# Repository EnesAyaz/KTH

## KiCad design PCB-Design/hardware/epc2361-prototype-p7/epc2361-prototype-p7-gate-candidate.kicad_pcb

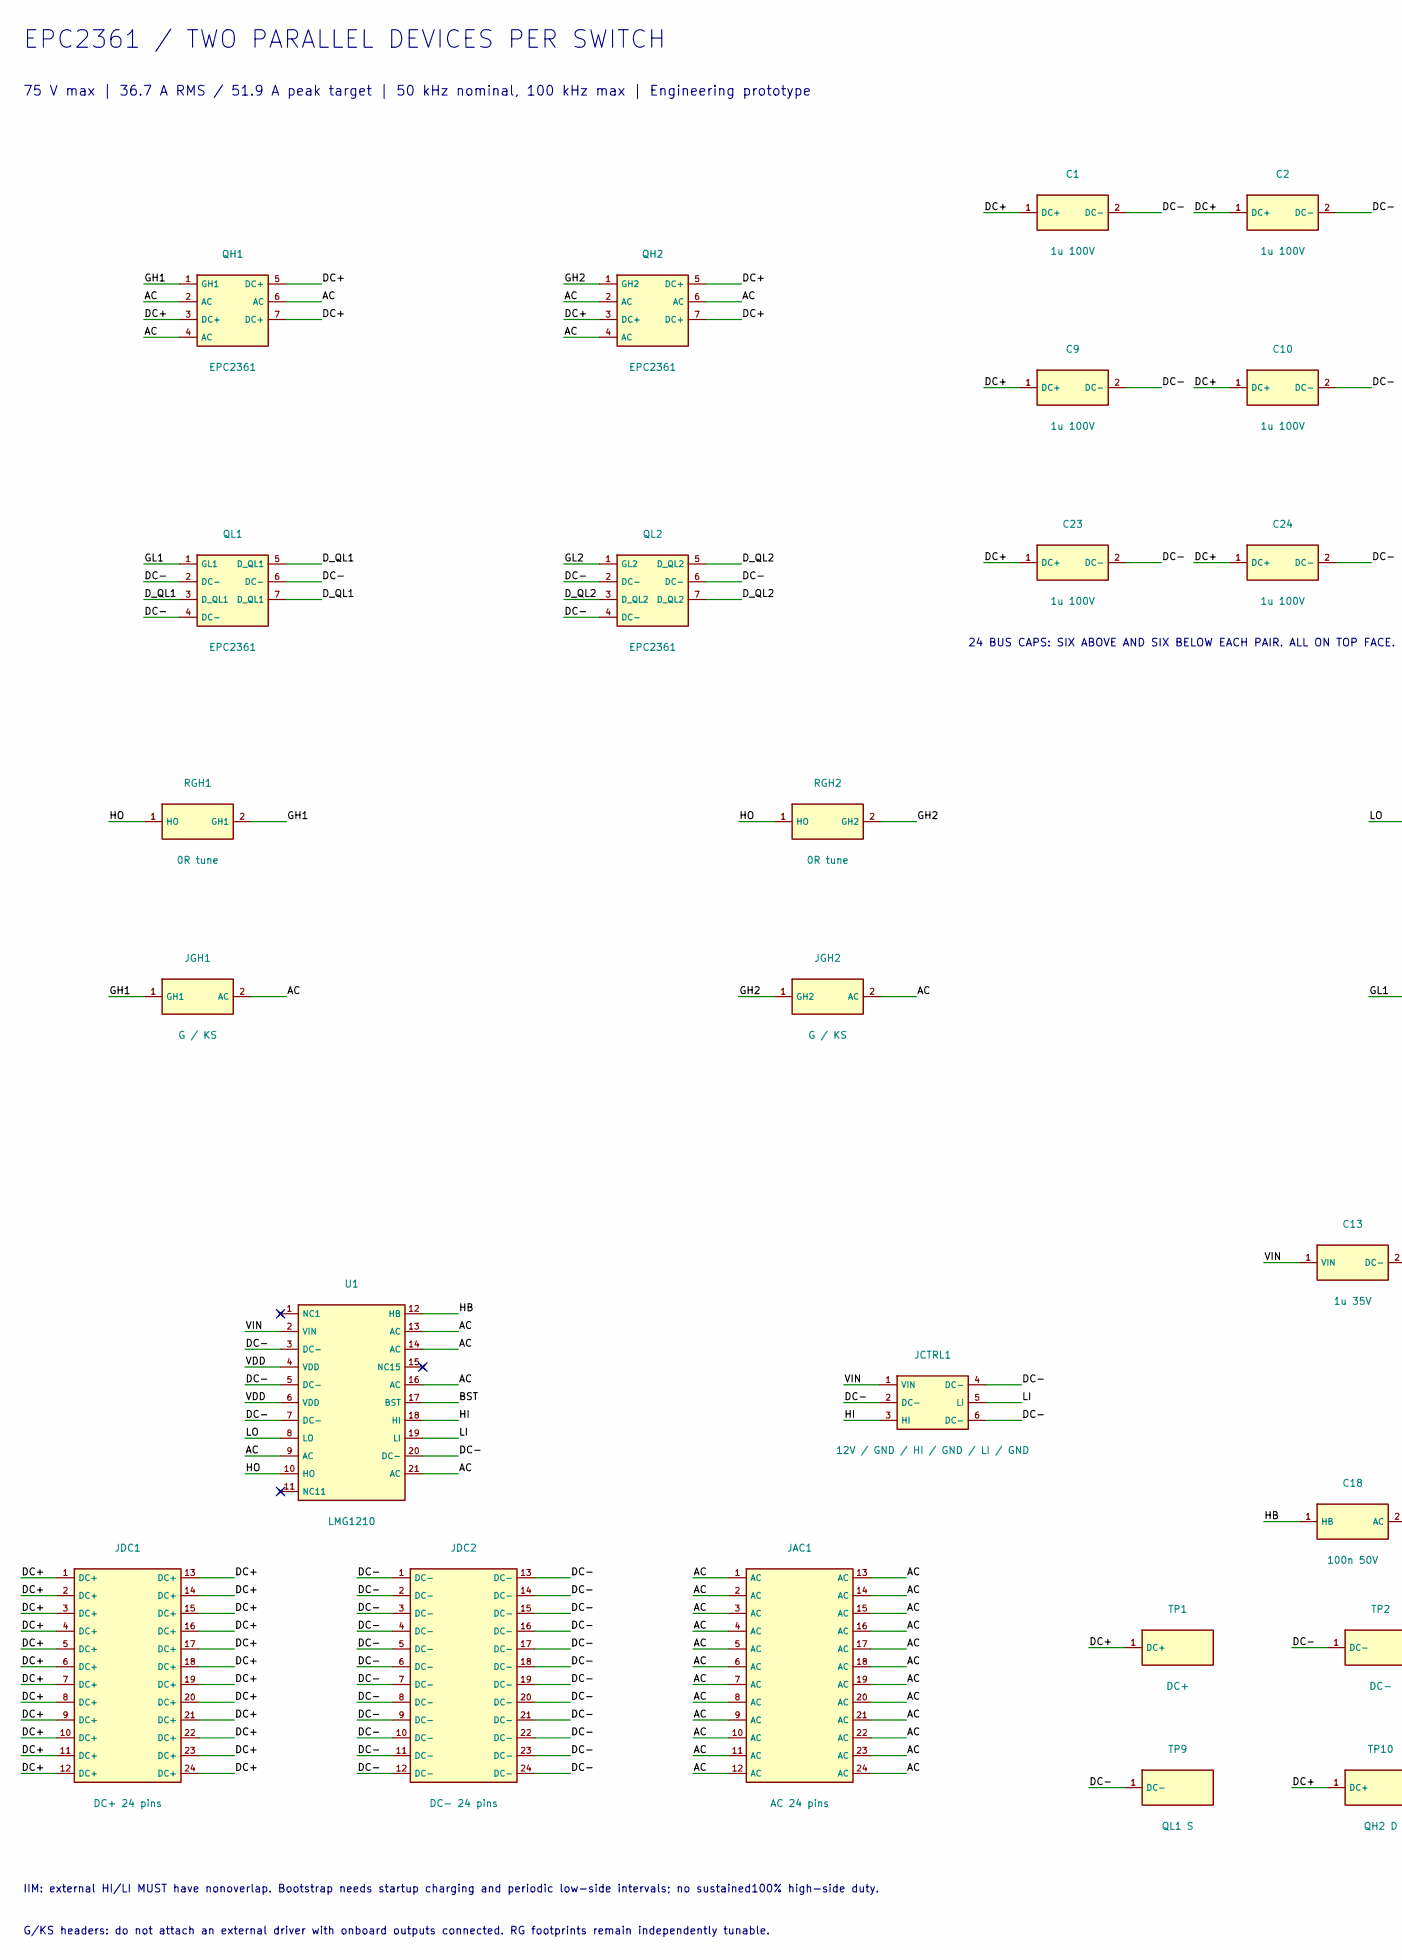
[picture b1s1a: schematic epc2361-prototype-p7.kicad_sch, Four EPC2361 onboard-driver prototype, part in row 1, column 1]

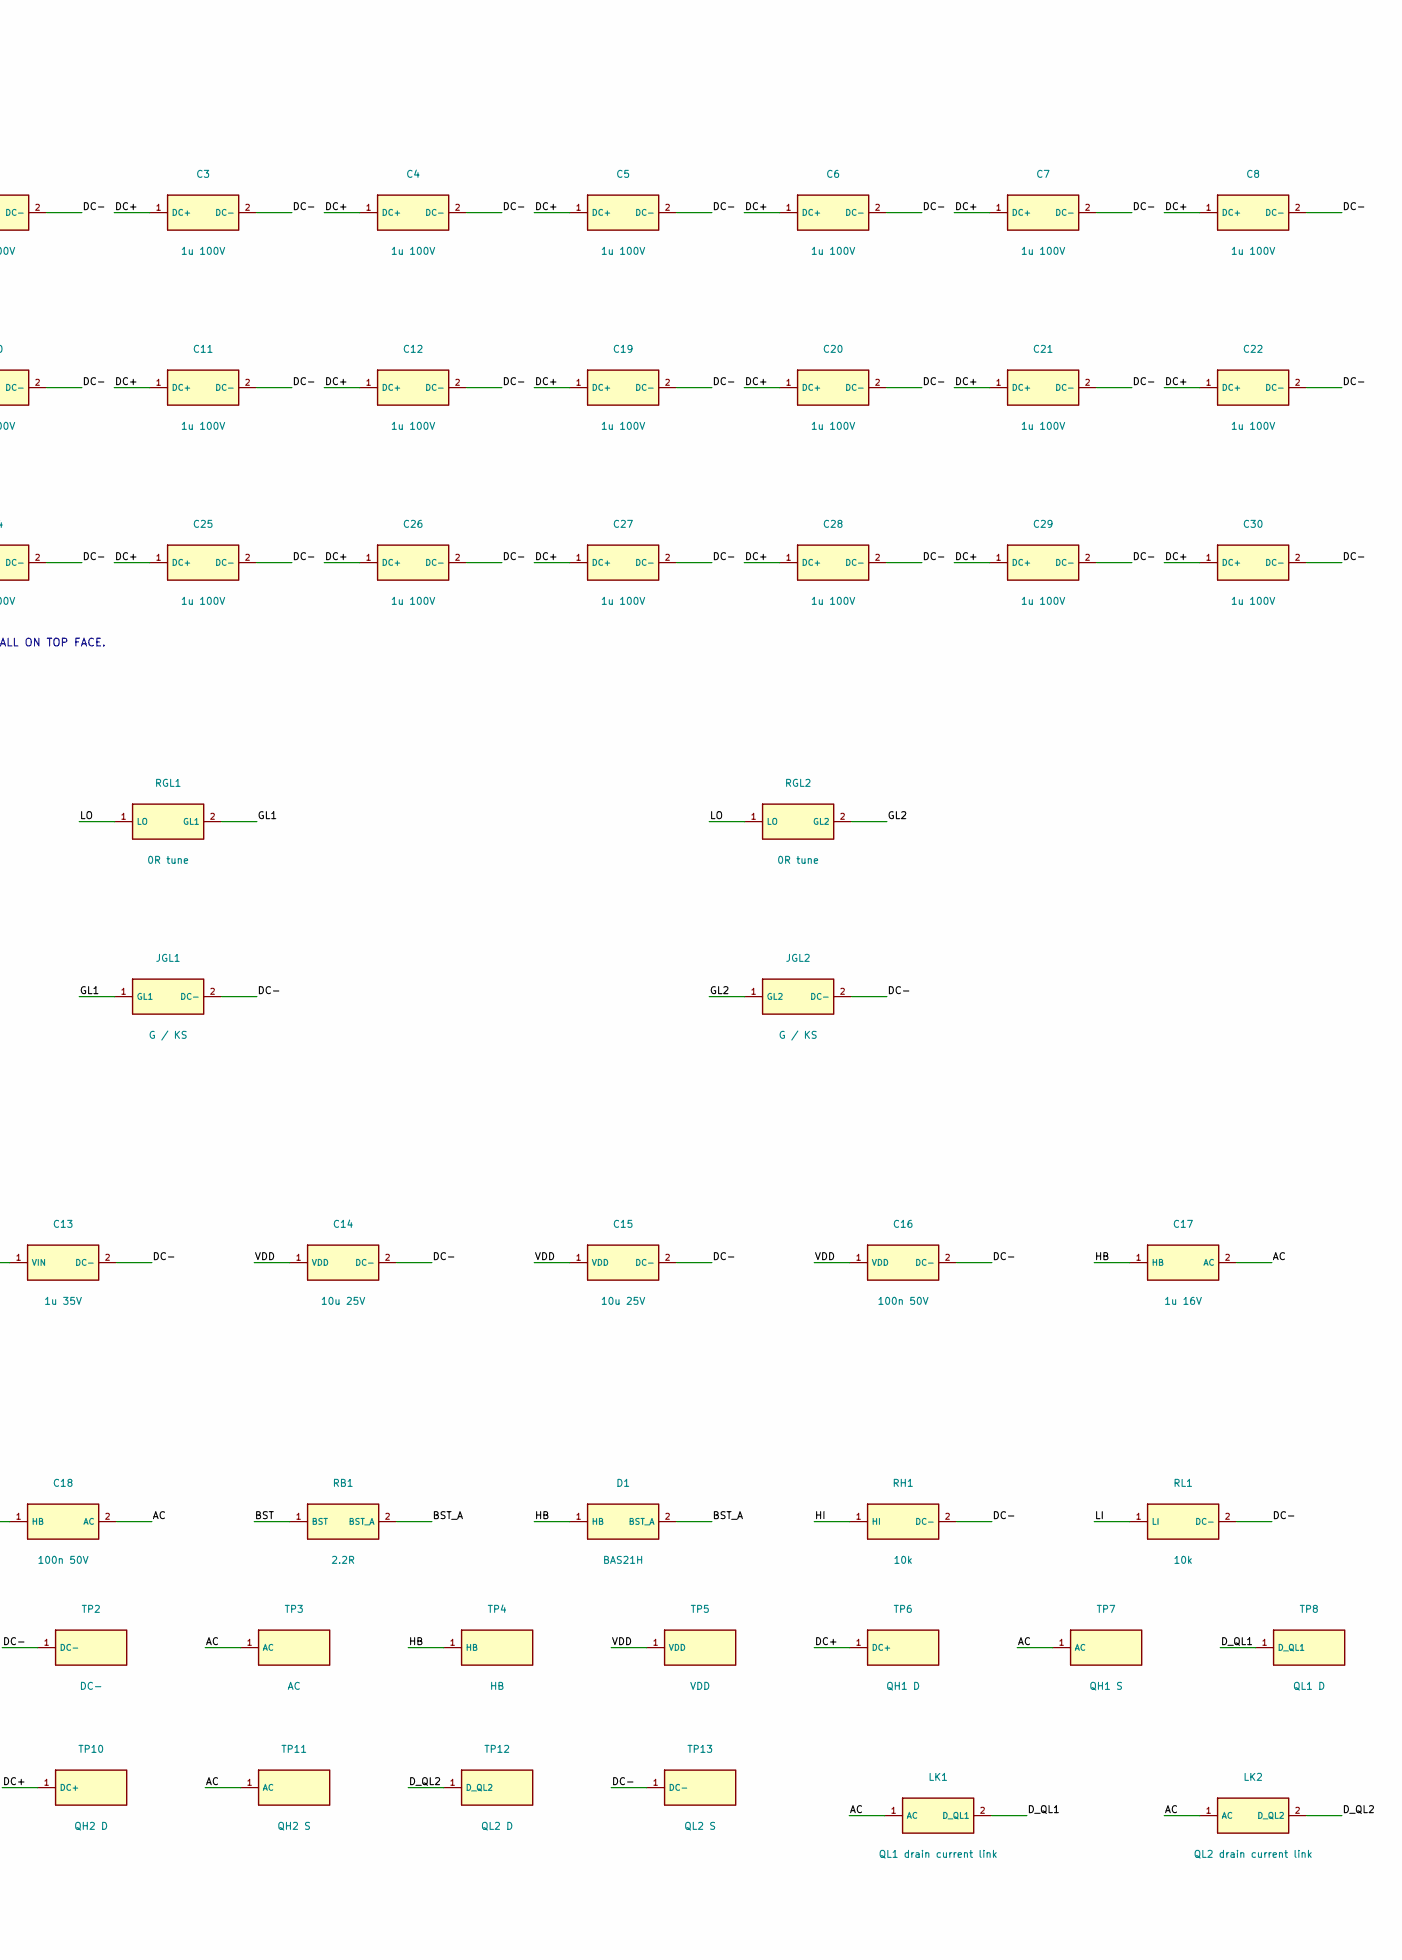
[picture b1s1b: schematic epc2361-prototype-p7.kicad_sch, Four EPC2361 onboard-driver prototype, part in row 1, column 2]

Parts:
C1, C2, C3, C4, C5, C6, C7, C8, C9, C10, C11, C12, C19, C20, C21, C22, C23, C24, C25, C26, C27, C28, C29, C30: 1u 100V; C_0805_2012Metric
C13: 1u 35V; C_0603_1608Metric
C14, C15: 10u 25V; C_0805_2012Metric
C16, C18: 100n 50V; C_0603_1608Metric
C17: 1u 16V; C_0603_1608Metric
D1: BAS21H; D_SOD-123F
JAC1: AC 24 pins; PinHeader_2x12_P2.54mm_Vertical
JCTRL1: 12V / GND / HI / GND / LI / GND; PinHeader_1x06_P2.54mm_Vertical
JDC1: DC+ 24 pins; PinHeader_2x12_P2.54mm_Vertical
JDC2: DC- 24 pins; PinHeader_2x12_P2.54mm_Vertical
JGH1, JGH2: G / KS; PinHeader_1x02_P1.27mm_Vertical
JGL1, JGL2: G / KS; PinHeader_1x02_P1.27mm_Vertical
LK1: QL1 drain current link; Current_Link
LK2: QL2 drain current link; Current_Link
QH1, QH2: EPC2361
QL1, QL2: EPC2361
RB1: 2.2R; R_0603_1608Metric
RGH1, RGH2: 0R tune; R_0402_1005Metric
RGL1, RGL2: 0R tune; R_0402_1005Metric
RH1: 10k; R_0402_1005Metric
RL1: 10k; R_0402_1005Metric
TP1: DC+; Probe_Pad
TP2: DC-; Probe_Pad
TP3: AC; Probe_Pad
TP4: HB; Probe_Pad
TP5: VDD; Probe_Pad
TP6: QH1 D; Probe_Pad
TP7: QH1 S; Probe_Pad
TP8: QL1 D; Probe_Pad
TP9: QL1 S; Probe_Pad
TP10: QH2 D; Probe_Pad
TP11: QH2 S; Probe_Pad
TP12: QL2 D; Probe_Pad
TP13: QL2 S; Probe_Pad
U1: LMG1210; LMG1210_RVR

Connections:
AC: C17.2 (AC), C18.2 (AC), JAC1.1, JAC1.2, JAC1.3, JAC1.4, JAC1.5, JAC1.6, JAC1.7, JAC1.8, JAC1.9, JAC1.10, JAC1.11, JAC1.12, JAC1.13, JAC1.14, JAC1.15, JAC1.16, JAC1.17, JAC1.18, JAC1.19, JAC1.20, JAC1.21, JAC1.22, JAC1.23, JAC1.24, JGH1.2 (AC), JGH2.2 (AC), LK1.1 (AC), LK2.1 (AC), QH1.2 (AC), QH1.4 (AC), QH1.6 (AC), QH2.2 (AC), QH2.4 (AC), QH2.6 (AC), TP3.1, TP7.1, TP11.1, U1.9 (AC), U1.13 (AC), U1.14 (AC), U1.16 (AC), U1.21 (AC)
BST: RB1.1 (BST), U1.17 (BST)
BST_A: D1.2 (BST_A), RB1.2 (BST_A)
DC+: C1.1 (DC+), C2.1 (DC+), C3.1 (DC+), C4.1 (DC+), C5.1 (DC+), C6.1 (DC+), C7.1 (DC+), C8.1 (DC+), C9.1 (DC+), C10.1 (DC+), C11.1 (DC+), C12.1 (DC+), C19.1 (DC+), C20.1 (DC+), C21.1 (DC+), C22.1 (DC+), C23.1 (DC+), C24.1 (DC+), C25.1 (DC+), C26.1 (DC+), C27.1 (DC+), C28.1 (DC+), C29.1 (DC+), C30.1 (DC+), JDC1.1, JDC1.2, JDC1.3, JDC1.4, JDC1.5, JDC1.6, JDC1.7, JDC1.8, JDC1.9, JDC1.10, JDC1.11, JDC1.12, JDC1.13, JDC1.14, JDC1.15, JDC1.16, JDC1.17, JDC1.18, JDC1.19, JDC1.20, JDC1.21, JDC1.22, JDC1.23, JDC1.24, QH1.3 (DC+), QH1.5 (DC+), QH1.7 (DC+), QH2.3 (DC+), QH2.5 (DC+), QH2.7 (DC+), TP1.1, TP6.1, TP10.1
DC-: C1.2 (DC-), C2.2 (DC-), C3.2 (DC-), C4.2 (DC-), C5.2 (DC-), C6.2 (DC-), C7.2 (DC-), C8.2 (DC-), C9.2 (DC-), C10.2 (DC-), C11.2 (DC-), C12.2 (DC-), C13.2 (DC-), C14.2 (DC-), C15.2 (DC-), C16.2 (DC-), C19.2 (DC-), C20.2 (DC-), C21.2 (DC-), C22.2 (DC-), C23.2 (DC-), C24.2 (DC-), C25.2 (DC-), C26.2 (DC-), C27.2 (DC-), C28.2 (DC-), C29.2 (DC-), C30.2 (DC-), JCTRL1.2 (DC-), JCTRL1.4 (DC-), JCTRL1.6 (DC-), JDC2.1, JDC2.2, JDC2.3, JDC2.4, JDC2.5, JDC2.6, JDC2.7, JDC2.8, JDC2.9, JDC2.10, JDC2.11, JDC2.12, JDC2.13, JDC2.14, JDC2.15, JDC2.16, JDC2.17, JDC2.18, JDC2.19, JDC2.20, JDC2.21, JDC2.22, JDC2.23, JDC2.24, JGL1.2 (DC-), JGL2.2 (DC-), QL1.2 (DC-), QL1.4 (DC-), QL1.6 (DC-), QL2.2 (DC-), QL2.4 (DC-), QL2.6 (DC-), RH1.2 (DC-), RL1.2 (DC-), TP2.1, TP9.1, TP13.1, U1.3 (DC-), U1.5 (DC-), U1.7 (DC-), U1.20 (DC-)
D_QL1: LK1.2 (D_QL1), QL1.3 (D_QL1), QL1.5 (D_QL1), QL1.7 (D_QL1), TP8.1
D_QL2: LK2.2 (D_QL2), QL2.3 (D_QL2), QL2.5 (D_QL2), QL2.7 (D_QL2), TP12.1
GH1: JGH1.1 (GH1), QH1.1 (GH1), RGH1.2 (GH1)
GH2: JGH2.1 (GH2), QH2.1 (GH2), RGH2.2 (GH2)
GL1: JGL1.1 (GL1), QL1.1 (GL1), RGL1.2 (GL1)
GL2: JGL2.1 (GL2), QL2.1 (GL2), RGL2.2 (GL2)
HB: C17.1 (HB), C18.1 (HB), D1.1 (HB), TP4.1, U1.12 (HB)
HI: JCTRL1.3 (HI), RH1.1 (HI), U1.18 (HI)
HO: RGH1.1 (HO), RGH2.1 (HO), U1.10 (HO)
LI: JCTRL1.5 (LI), RL1.1 (LI), U1.19 (LI)
LO: RGL1.1 (LO), RGL2.1 (LO), U1.8 (LO)
NC1: U1.1 (NC1)
NC11: U1.11 (NC11)
NC15: U1.15 (NC15)
VDD: C14.1 (VDD), C15.1 (VDD), C16.1 (VDD), TP5.1, U1.4 (VDD), U1.6 (VDD)
VIN: C13.1 (VIN), JCTRL1.1 (VIN), U1.2 (VIN)

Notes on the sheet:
EPC2361 / TWO PARALLEL DEVICES PER SWITCH
75 V max | 36.7 A RMS / 51.9 A peak target | 50 kHz nominal, 100 kHz max | Engineering prototype
24 BUS CAPS: SIX ABOVE AND SIX BELOW EACH PAIR. ALL ON TOP FACE.
IIM: external HI/LI MUST have nonoverlap. Bootstrap needs startup charging and periodic low-side intervals; no sustained100% high-side duty.
G/KS headers: do not attach an external driver with onboard outputs connected. RG footprints remain independently tunable.

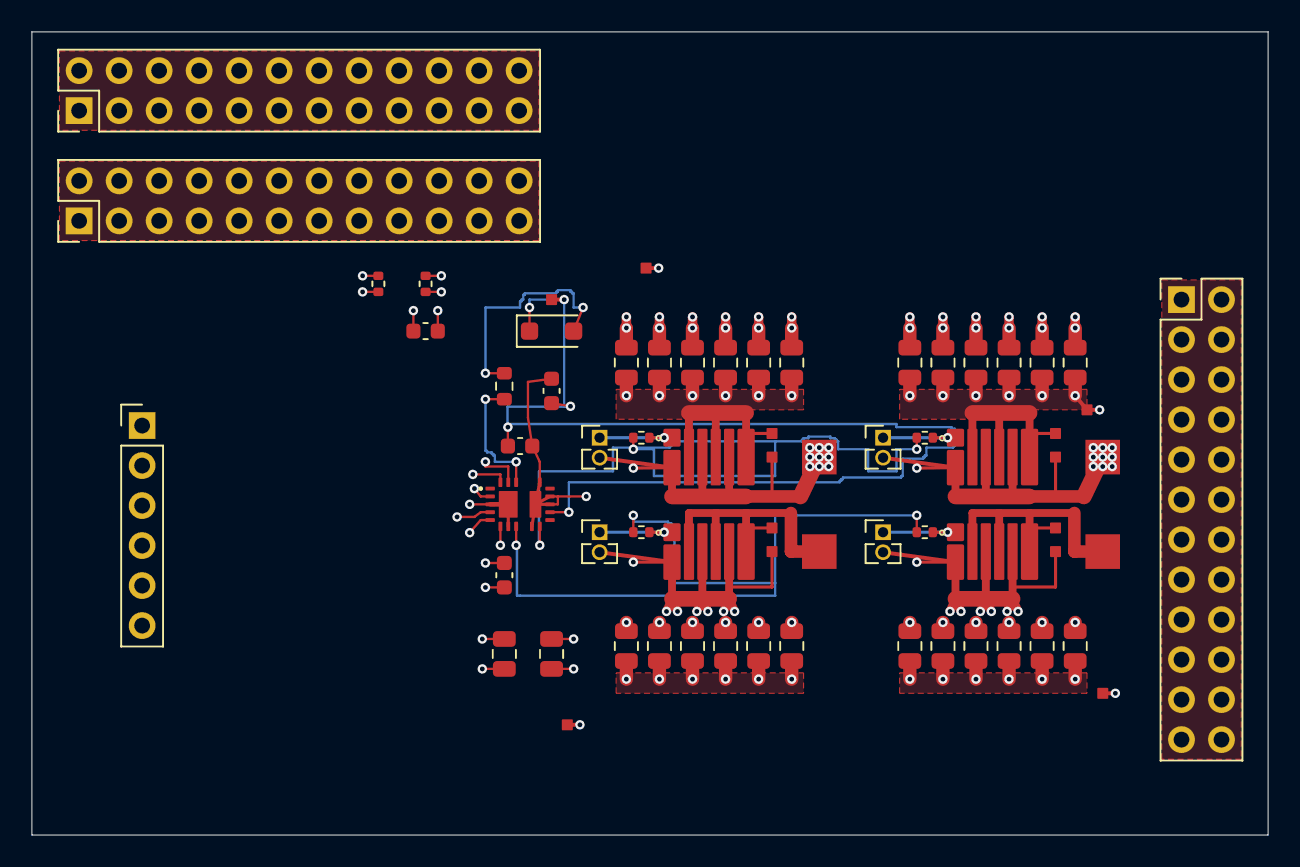
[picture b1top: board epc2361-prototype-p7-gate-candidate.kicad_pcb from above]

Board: 4 copper layers, 78.5 x 51.0 mm, 66 parts (0 on the bottom side), 18 nets.

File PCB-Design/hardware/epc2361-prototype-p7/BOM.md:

# Prototype BOM

All quantities are for one four-FET board. Provisional engineering BOM; not purchasing release.

| References | Qty | MPN | Value | Footprint | Fit | Notes |
|---|---:|---|---|---|---|---|
| QH1, QL1, QH2, QL2 | 4 | EPC2361 | EPC2361 | epc2361-prototype:EPC2361 | Fit |  |
| C1, C2, C3, C4, C5, C6, C7, C8, C9, C10, C11, C12, C19, C25, C20, C26, C21, C27, C22, C28, C23, C29, C24, C30 | 24 | C2012X7S2A105K125AB | 1u 100V | Capacitor_SMD:C_0805_2012Metric | Fit |  |
| RGH1, RGL1, RGH2, RGL2 | 4 | RC0402JR-070RL | 0R tune | Resistor_SMD:R_0402_1005Metric | Fit | Individual gate damping footprint. Tune during double-pulse testing. |
| JGH1, JGL1, JGH2, JGL2 | 4 | FTS-102-01-L-S | G / KS | Connector_PinHeader_1.27mm:PinHeader_1x02_P1.27mm_Vertical | Fit | Measurement/external-drive header; never connect a second active driver. Remove local series resistor to isolate onboard output. Generic footprint: verify manufacturer drawing before release. |
| JDC1 | 1 | TSW-112-07-G-D | DC+ 24 pins | Connector_PinHeader_2.54mm:PinHeader_2x12_P2.54mm_Vertical | Fit | 24 parallel contacts. Full-array mating/thermal validation required; no single-pin current multiplication. Generic package model. |
| JDC2 | 1 | TSW-112-07-G-D | DC- 24 pins | Connector_PinHeader_2.54mm:PinHeader_2x12_P2.54mm_Vertical | Fit | 24 parallel contacts. Full-array mating/thermal validation required; no single-pin current multiplication. Generic package model. |
| JAC1 | 1 | TSW-112-07-G-D | AC 24 pins | Connector_PinHeader_2.54mm:PinHeader_2x12_P2.54mm_Vertical | Fit | 24 parallel contacts. Full-array mating/thermal validation required; no single-pin current multiplication. Generic package model. |
| U1 | 1 | LMG1210RVRR | LMG1210 | epc2361-prototype:LMG1210_RVR | Fit | IIM: external nonoverlapping HI/LI; no internal shoot-through interlock in this mode. |
| JCTRL1 | 1 | TSW-106-07-G-S | 12V / GND / HI / GND / LI / GND | Connector_PinHeader_2.54mm:PinHeader_1x06_P2.54mm_Vertical | Fit |  |
| C13 | 1 | C1608X7R1V105K080AC | 1u 35V | Capacitor_SMD:C_0603_1608Metric | Fit | Verify effective capacitance and temperature; VDD X5R parts rated85C. |
| C14, C15 | 2 | C2012X5R1E106K125AB | 10u 25V | Capacitor_SMD:C_0805_2012Metric | Fit | Verify effective capacitance and temperature; VDD X5R parts rated85C. |
| C16, C18 | 2 | C1608X7R1H104K080AA | 100n 50V | Capacitor_SMD:C_0603_1608Metric | Fit | Verify effective capacitance and temperature; VDD X5R parts rated85C. |
| C17 | 1 | C1608X7R1C105K080AC | 1u 16V | Capacitor_SMD:C_0603_1608Metric | Fit | Verify effective capacitance and temperature; VDD X5R parts rated85C. |
| RB1 | 1 | RC0603FR-072R2L | 2.2R | Resistor_SMD:R_0603_1608Metric | Fit |  |
| D1 | 1 | BAS21H,115 | BAS21H | Diode_SMD:D_SOD-123F | Fit | External bootstrap diode: cathode HB, anode BST_A. Not a bootstrap voltage clamp. |
| RH1, RL1 | 2 | RC0402FR-0710KL | 10k | Resistor_SMD:R_0402_1005Metric | Fit |  |
| TP1 | 1 | PCB copper test pad | DC+ | epc2361-prototype:Probe_Pad | Fit | PCB feature; no purchased component. |
| TP2 | 1 | PCB copper test pad | DC- | epc2361-prototype:Probe_Pad | Fit | PCB feature; no purchased component. |
| TP3 | 1 | PCB copper test pad | AC | epc2361-prototype:Probe_Pad | Fit | PCB feature; no purchased component. |
| TP4 | 1 | PCB copper test pad | HB | epc2361-prototype:Probe_Pad | Fit | PCB feature; no purchased component. |
| TP5 | 1 | PCB copper test pad | VDD | epc2361-prototype:Probe_Pad | Fit | PCB feature; no purchased component. |
| TP6 | 1 | PCB copper test pad | QH1 D | epc2361-prototype:Probe_Pad | Fit | Local VDS spring-tip contact; 1.5 mm D/S spacing, verify actual probe accessory. High-side source is AC, not earth. |
| TP7 | 1 | PCB copper test pad | QH1 S | epc2361-prototype:Probe_Pad | Fit | Local VDS spring-tip contact; 1.5 mm D/S spacing, verify actual probe accessory. High-side source is AC, not earth. |
| TP8 | 1 | PCB copper test pad | QL1 D | epc2361-prototype:Probe_Pad | Fit | Local VDS spring-tip contact; 1.5 mm D/S spacing, verify actual probe accessory. High-side source is AC, not earth. |
| TP9 | 1 | PCB copper test pad | QL1 S | epc2361-prototype:Probe_Pad | Fit | Local VDS spring-tip contact; 1.5 mm D/S spacing, verify actual probe accessory. High-side source is AC, not earth. |
| TP10 | 1 | PCB copper test pad | QH2 D | epc2361-prototype:Probe_Pad | Fit | Local VDS spring-tip contact; 1.5 mm D/S spacing, verify actual probe accessory. High-side source is AC, not earth. |
| TP11 | 1 | PCB copper test pad | QH2 S | epc2361-prototype:Probe_Pad | Fit | Local VDS spring-tip contact; 1.5 mm D/S spacing, verify actual probe accessory. High-side source is AC, not earth. |
| TP12 | 1 | PCB copper test pad | QL2 D | epc2361-prototype:Probe_Pad | Fit | Local VDS spring-tip contact; 1.5 mm D/S spacing, verify actual probe accessory. High-side source is AC, not earth. |
| TP13 | 1 | PCB copper test pad | QL2 S | epc2361-prototype:Probe_Pad | Fit | Local VDS spring-tip contact; 1.5 mm D/S spacing, verify actual probe accessory. High-side source is AC, not earth. |
| LK1 | 1 | CUSTOM-CU-LINK-P7 | QL1 drain current link | epc2361-prototype:Current_Link | Fit | Matched formed copper current link, one per low-side device. 2mm wide x0.5mm thick, 6mm land pitch, 5mm underside rise. Hand solder. Coil closure/cable exit and parasitic matching require verification. |
| LK2 | 1 | CUSTOM-CU-LINK-P7 | QL2 drain current link | epc2361-prototype:Current_Link | Fit | Matched formed copper current link, one per low-side device. 2mm wide x0.5mm thick, 6mm land pitch, 5mm underside rise. Hand solder. Coil closure/cable exit and parasitic matching require verification. |

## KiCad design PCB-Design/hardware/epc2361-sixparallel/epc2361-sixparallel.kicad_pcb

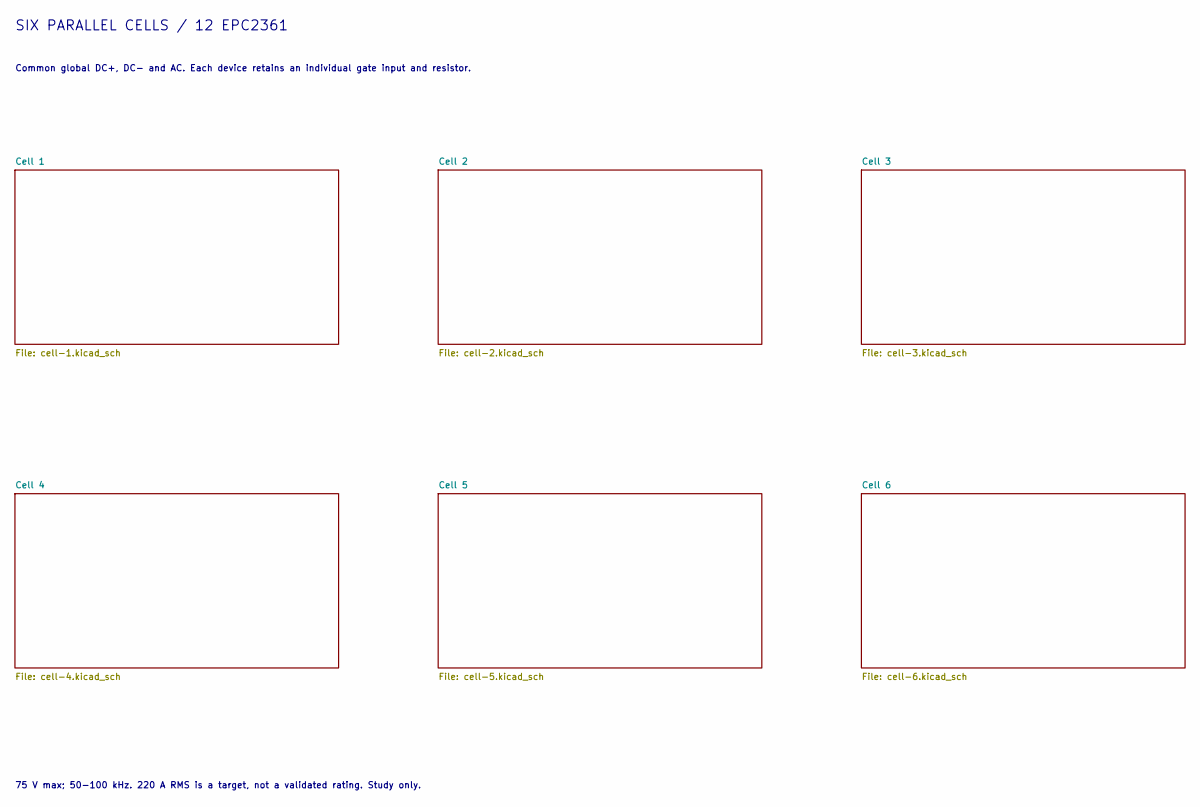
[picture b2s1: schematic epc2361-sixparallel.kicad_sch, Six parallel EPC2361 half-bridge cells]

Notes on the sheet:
SIX PARALLEL CELLS / 12 EPC2361
Common global DC+, DC- and AC. Each device retains an individual gate input and resistor.
75 V max; 50-100 kHz. 220 A RMS is a target, not a validated rating. Study only.

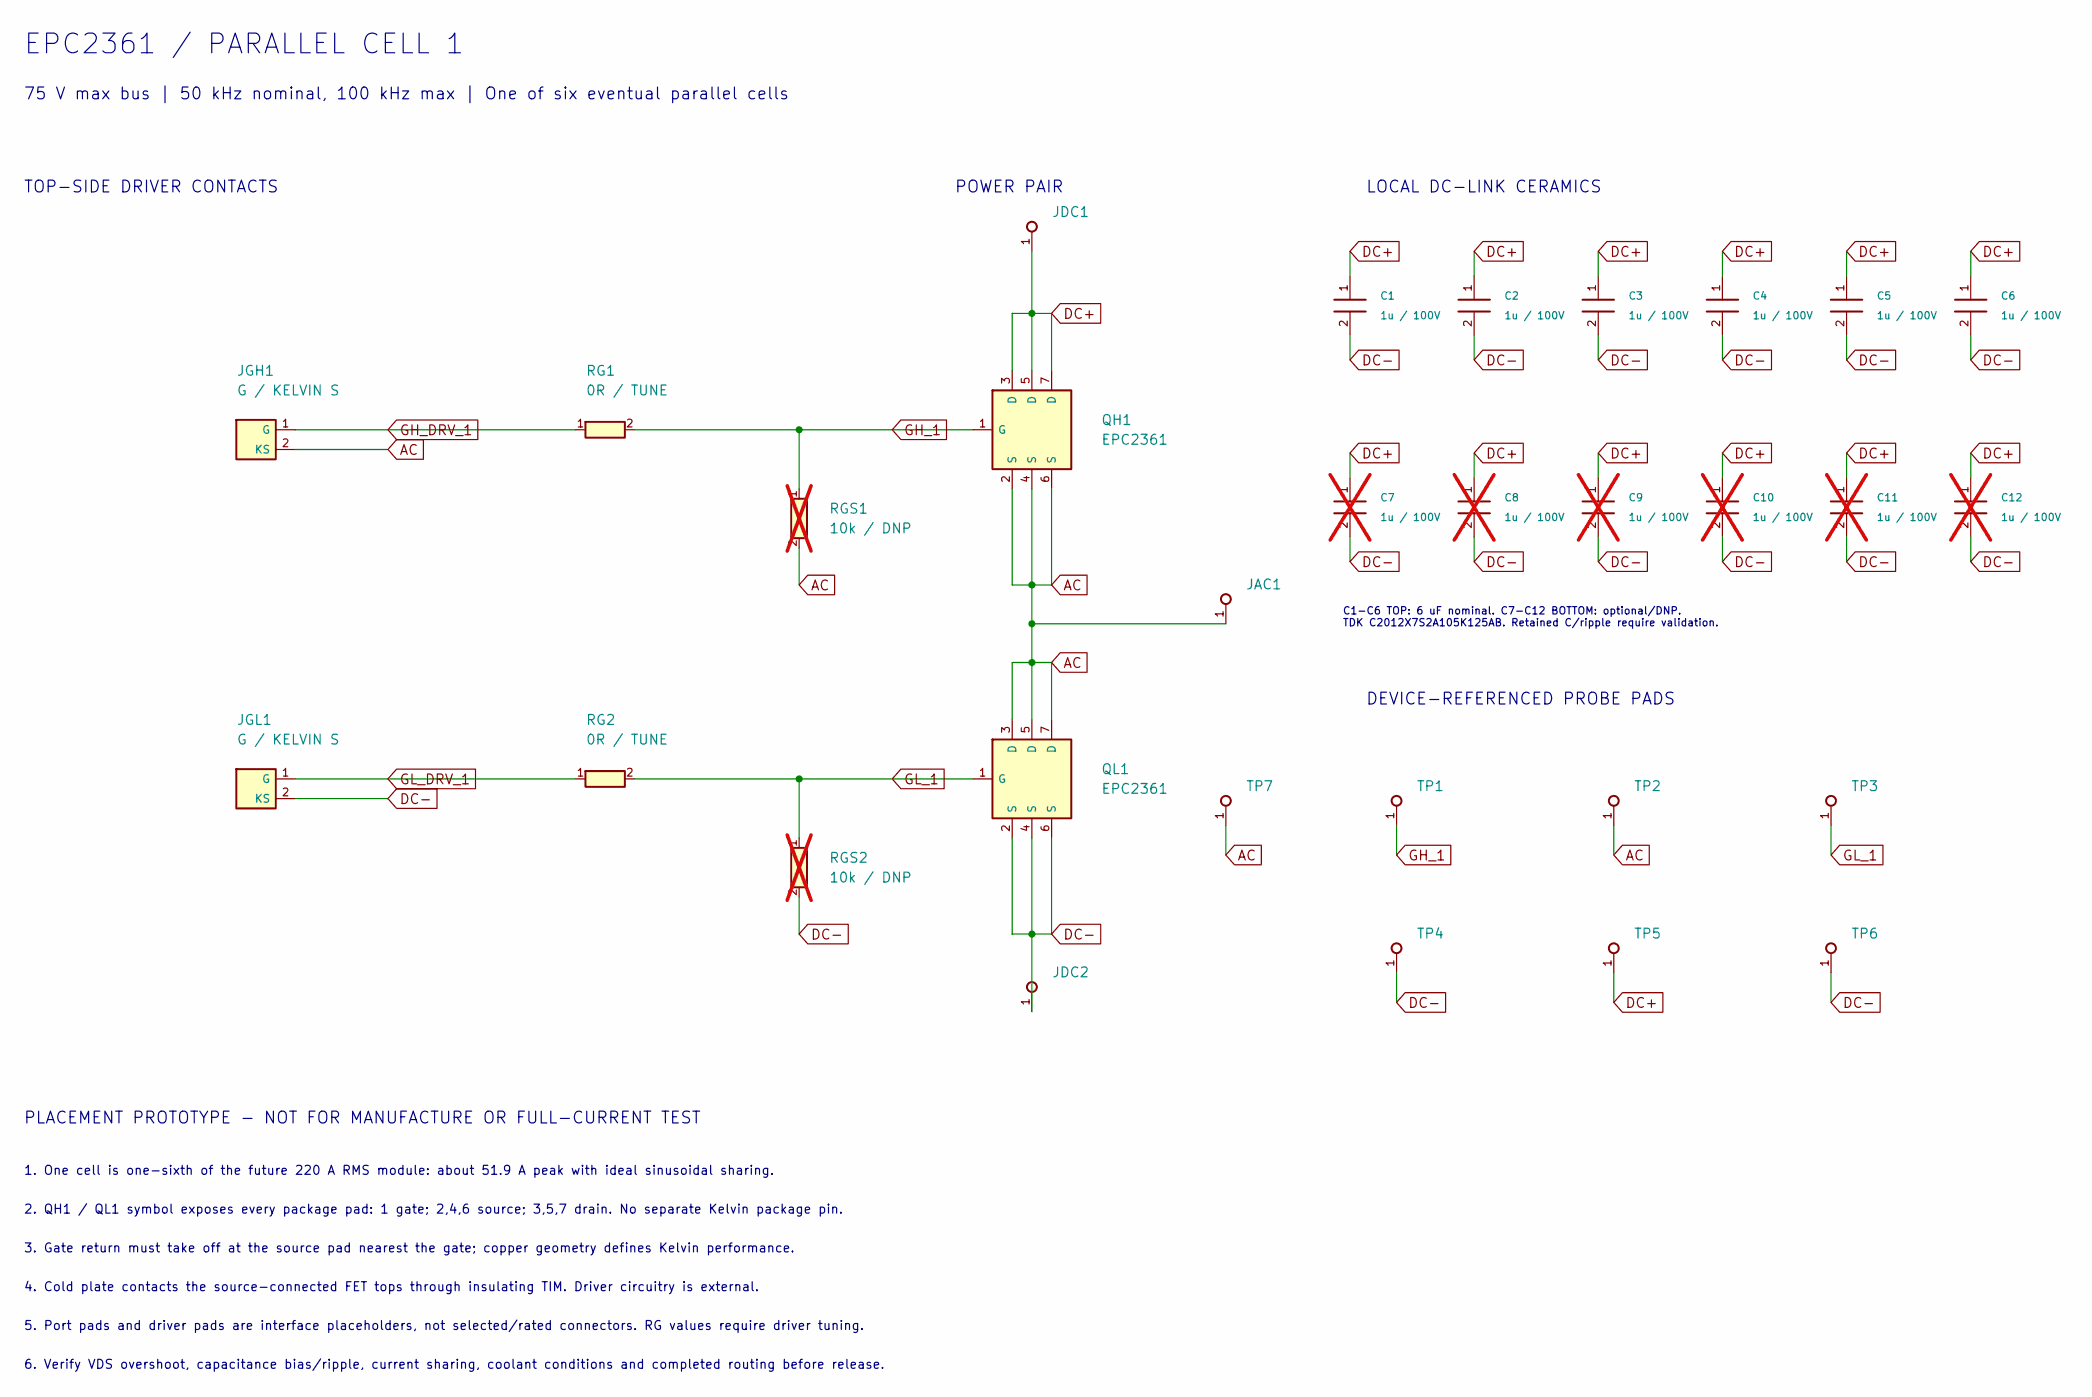
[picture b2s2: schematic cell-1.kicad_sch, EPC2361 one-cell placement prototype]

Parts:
C1, C2, C3, C4, C5, C6: 1u / 100V; C_0805_2012Metric
C7, C8, C9, C10, C11, C12: 1u / 100V; C_0805_2012Metric; not fitted
JAC1: AC PORT PAD; Power_Port_Pad
JDC1: DC+ PORT PAD; Power_Port_Pad
JDC2: DC- PORT PAD; Power_Port_Pad
JGH1: G / KELVIN S; Gate_Source_Pads
JGL1: G / KELVIN S; Gate_Source_Pads
QH1: EPC2361
QL1: EPC2361
RG1, RG2: 0R / TUNE; R_0402_1005Metric
RGS1, RGS2: 10k / DNP; R_0402_1005Metric; not fitted
TP1: GH; Probe_Pad
TP2, TP7: AC; Probe_Pad
TP3: GL; Probe_Pad
TP4, TP6: DC-; Probe_Pad
TP5: DC+; Probe_Pad

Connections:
AC: JAC1.1, JGH1.2 (KS), QH1.2 (S), QH1.4 (S), QH1.6 (S), QL1.3 (D), QL1.5 (D), QL1.7 (D), RGS1.2, TP2.1, TP7.1; also elsewhere on the board
DC+: C1.1, C2.1, C3.1, C4.1, C5.1, C6.1, C7.1, C8.1, C9.1, C10.1, C11.1, C12.1, JDC1.1, QH1.3 (D), QH1.5 (D), QH1.7 (D), TP5.1; also elsewhere on the board
DC-: C1.2, C2.2, C3.2, C4.2, C5.2, C6.2, C7.2, C8.2, C9.2, C10.2, C11.2, C12.2, JDC2.1, JGL1.2 (KS), QL1.2 (S), QL1.4 (S), QL1.6 (S), RGS2.2, TP4.1, TP6.1; also elsewhere on the board
GH_1: QH1.1 (G), RG1.2, RGS1.1, TP1.1
GH_DRV_1: JGH1.1 (G), RG1.1
GL_1: QL1.1 (G), RG2.2, RGS2.1, TP3.1
GL_DRV_1: JGL1.1 (G), RG2.1

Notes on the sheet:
EPC2361 / PARALLEL CELL 1
75 V max bus | 50 kHz nominal, 100 kHz max | One of six eventual parallel cells
TOP-SIDE DRIVER CONTACTS
POWER PAIR
LOCAL DC-LINK CERAMICS
C1-C6 TOP: 6 uF nominal. C7-C12 BOTTOM: optional/DNP. TDK C2012X7S2A105K125AB. Retained C/ripple require validation.
DEVICE-REFERENCED PROBE PADS
PLACEMENT PROTOTYPE - NOT FOR MANUFACTURE OR FULL-CURRENT TEST
1. One cell is one-sixth of the future 220 A RMS module: about 51.9 A peak with ideal sinusoidal sharing.
2. QH1 / QL1 symbol exposes every package pad: 1 gate; 2,4,6 source; 3,5,7 drain. No separate Kelvin package pin.
3. Gate return must take off at the source pad nearest the gate; copper geometry defines Kelvin performance.
4. Cold plate contacts the source-connected FET tops through insulating TIM. Driver circuitry is external.
5. Port pads and driver pads are interface placeholders, not selected/rated connectors. RG values require driver tuning.
6. Verify VDS overshoot, capacitance bias/ripple, current sharing, coolant conditions and completed routing before release.

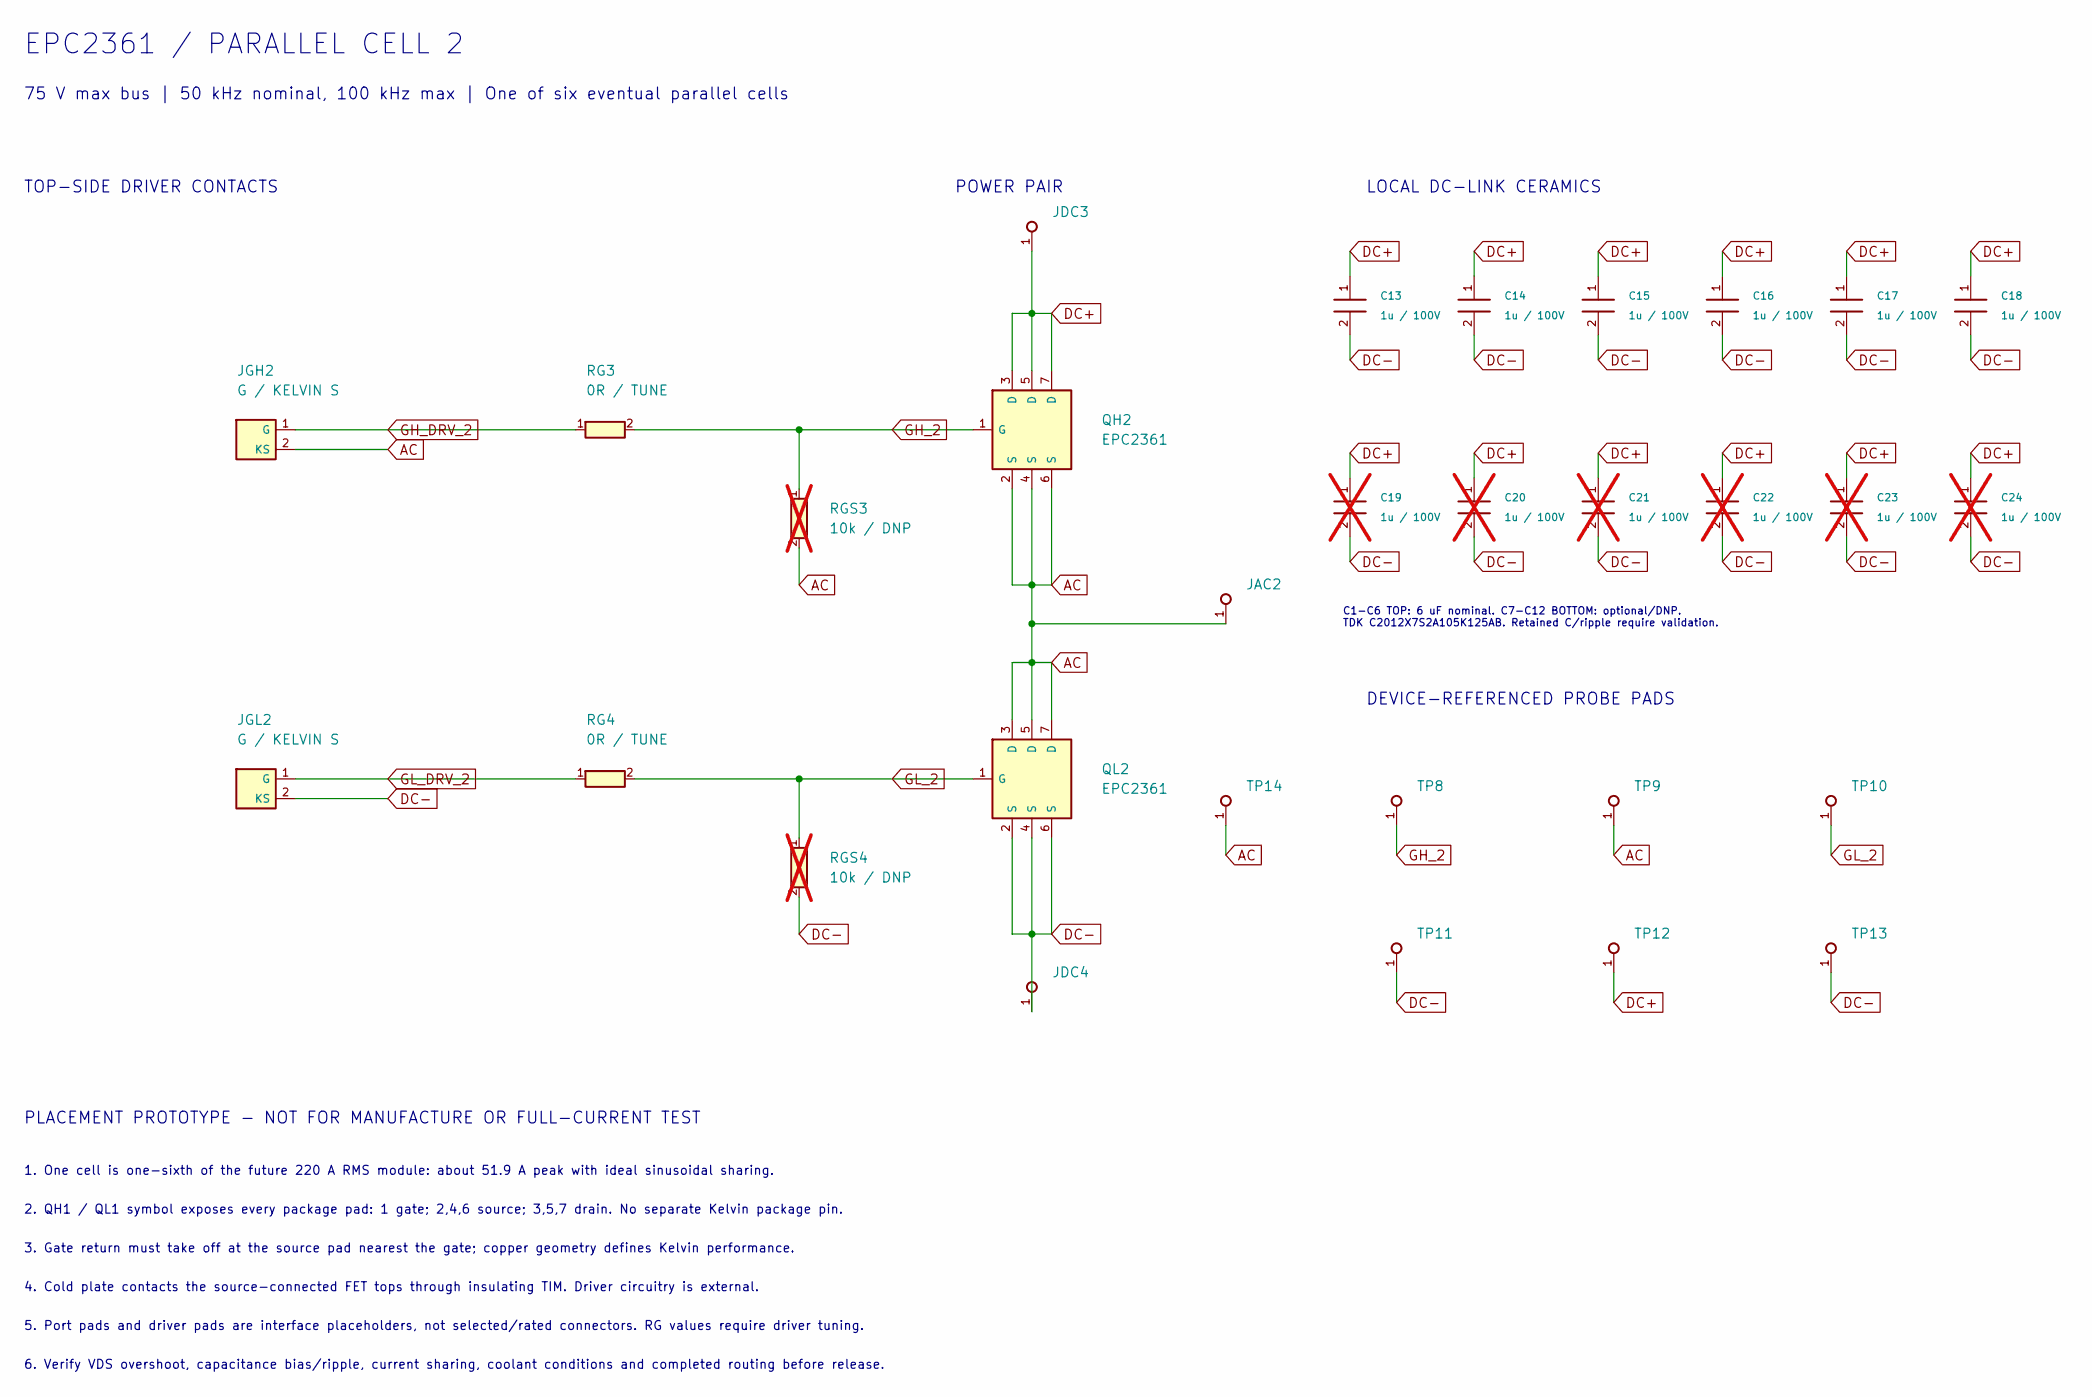
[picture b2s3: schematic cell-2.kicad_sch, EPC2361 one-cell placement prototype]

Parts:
C13, C14, C15, C16, C17, C18: 1u / 100V; C_0805_2012Metric
C19, C20, C21, C22, C23, C24: 1u / 100V; C_0805_2012Metric; not fitted
JAC2: AC PORT PAD; Power_Port_Pad
JDC3: DC+ PORT PAD; Power_Port_Pad
JDC4: DC- PORT PAD; Power_Port_Pad
JGH2: G / KELVIN S; Gate_Source_Pads
JGL2: G / KELVIN S; Gate_Source_Pads
QH2: EPC2361
QL2: EPC2361
RG3, RG4: 0R / TUNE; R_0402_1005Metric
RGS3, RGS4: 10k / DNP; R_0402_1005Metric; not fitted
TP8: GH; Probe_Pad
TP9, TP14: AC; Probe_Pad
TP10: GL; Probe_Pad
TP11, TP13: DC-; Probe_Pad
TP12: DC+; Probe_Pad

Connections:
AC: JAC2.1, JGH2.2 (KS), QH2.2 (S), QH2.4 (S), QH2.6 (S), QL2.3 (D), QL2.5 (D), QL2.7 (D), RGS3.2, TP9.1, TP14.1; also elsewhere on the board
DC+: C13.1, C14.1, C15.1, C16.1, C17.1, C18.1, C19.1, C20.1, C21.1, C22.1, C23.1, C24.1, JDC3.1, QH2.3 (D), QH2.5 (D), QH2.7 (D), TP12.1; also elsewhere on the board
DC-: C13.2, C14.2, C15.2, C16.2, C17.2, C18.2, C19.2, C20.2, C21.2, C22.2, C23.2, C24.2, JDC4.1, JGL2.2 (KS), QL2.2 (S), QL2.4 (S), QL2.6 (S), RGS4.2, TP11.1, TP13.1; also elsewhere on the board
GH_2: QH2.1 (G), RG3.2, RGS3.1, TP8.1
GH_DRV_2: JGH2.1 (G), RG3.1
GL_2: QL2.1 (G), RG4.2, RGS4.1, TP10.1
GL_DRV_2: JGL2.1 (G), RG4.1

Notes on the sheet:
EPC2361 / PARALLEL CELL 2
75 V max bus | 50 kHz nominal, 100 kHz max | One of six eventual parallel cells
TOP-SIDE DRIVER CONTACTS
POWER PAIR
LOCAL DC-LINK CERAMICS
C1-C6 TOP: 6 uF nominal. C7-C12 BOTTOM: optional/DNP. TDK C2012X7S2A105K125AB. Retained C/ripple require validation.
DEVICE-REFERENCED PROBE PADS
PLACEMENT PROTOTYPE - NOT FOR MANUFACTURE OR FULL-CURRENT TEST
1. One cell is one-sixth of the future 220 A RMS module: about 51.9 A peak with ideal sinusoidal sharing.
2. QH1 / QL1 symbol exposes every package pad: 1 gate; 2,4,6 source; 3,5,7 drain. No separate Kelvin package pin.
3. Gate return must take off at the source pad nearest the gate; copper geometry defines Kelvin performance.
4. Cold plate contacts the source-connected FET tops through insulating TIM. Driver circuitry is external.
5. Port pads and driver pads are interface placeholders, not selected/rated connectors. RG values require driver tuning.
6. Verify VDS overshoot, capacitance bias/ripple, current sharing, coolant conditions and completed routing before release.
